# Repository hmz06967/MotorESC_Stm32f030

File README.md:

# MOTOR ESC CARD DESIGN FROM EAGLE CAD

Working please download and test 

#### video (https://www.youtube.com/watch?v=FIM-RrpVAwA)

firmware https://github.com/hmz06967/MotorEsc_Firmware

## Ekran Görüntüleri

#### Copyright (C) 2021 [OZK](https://hamzaozkan.com.tr)

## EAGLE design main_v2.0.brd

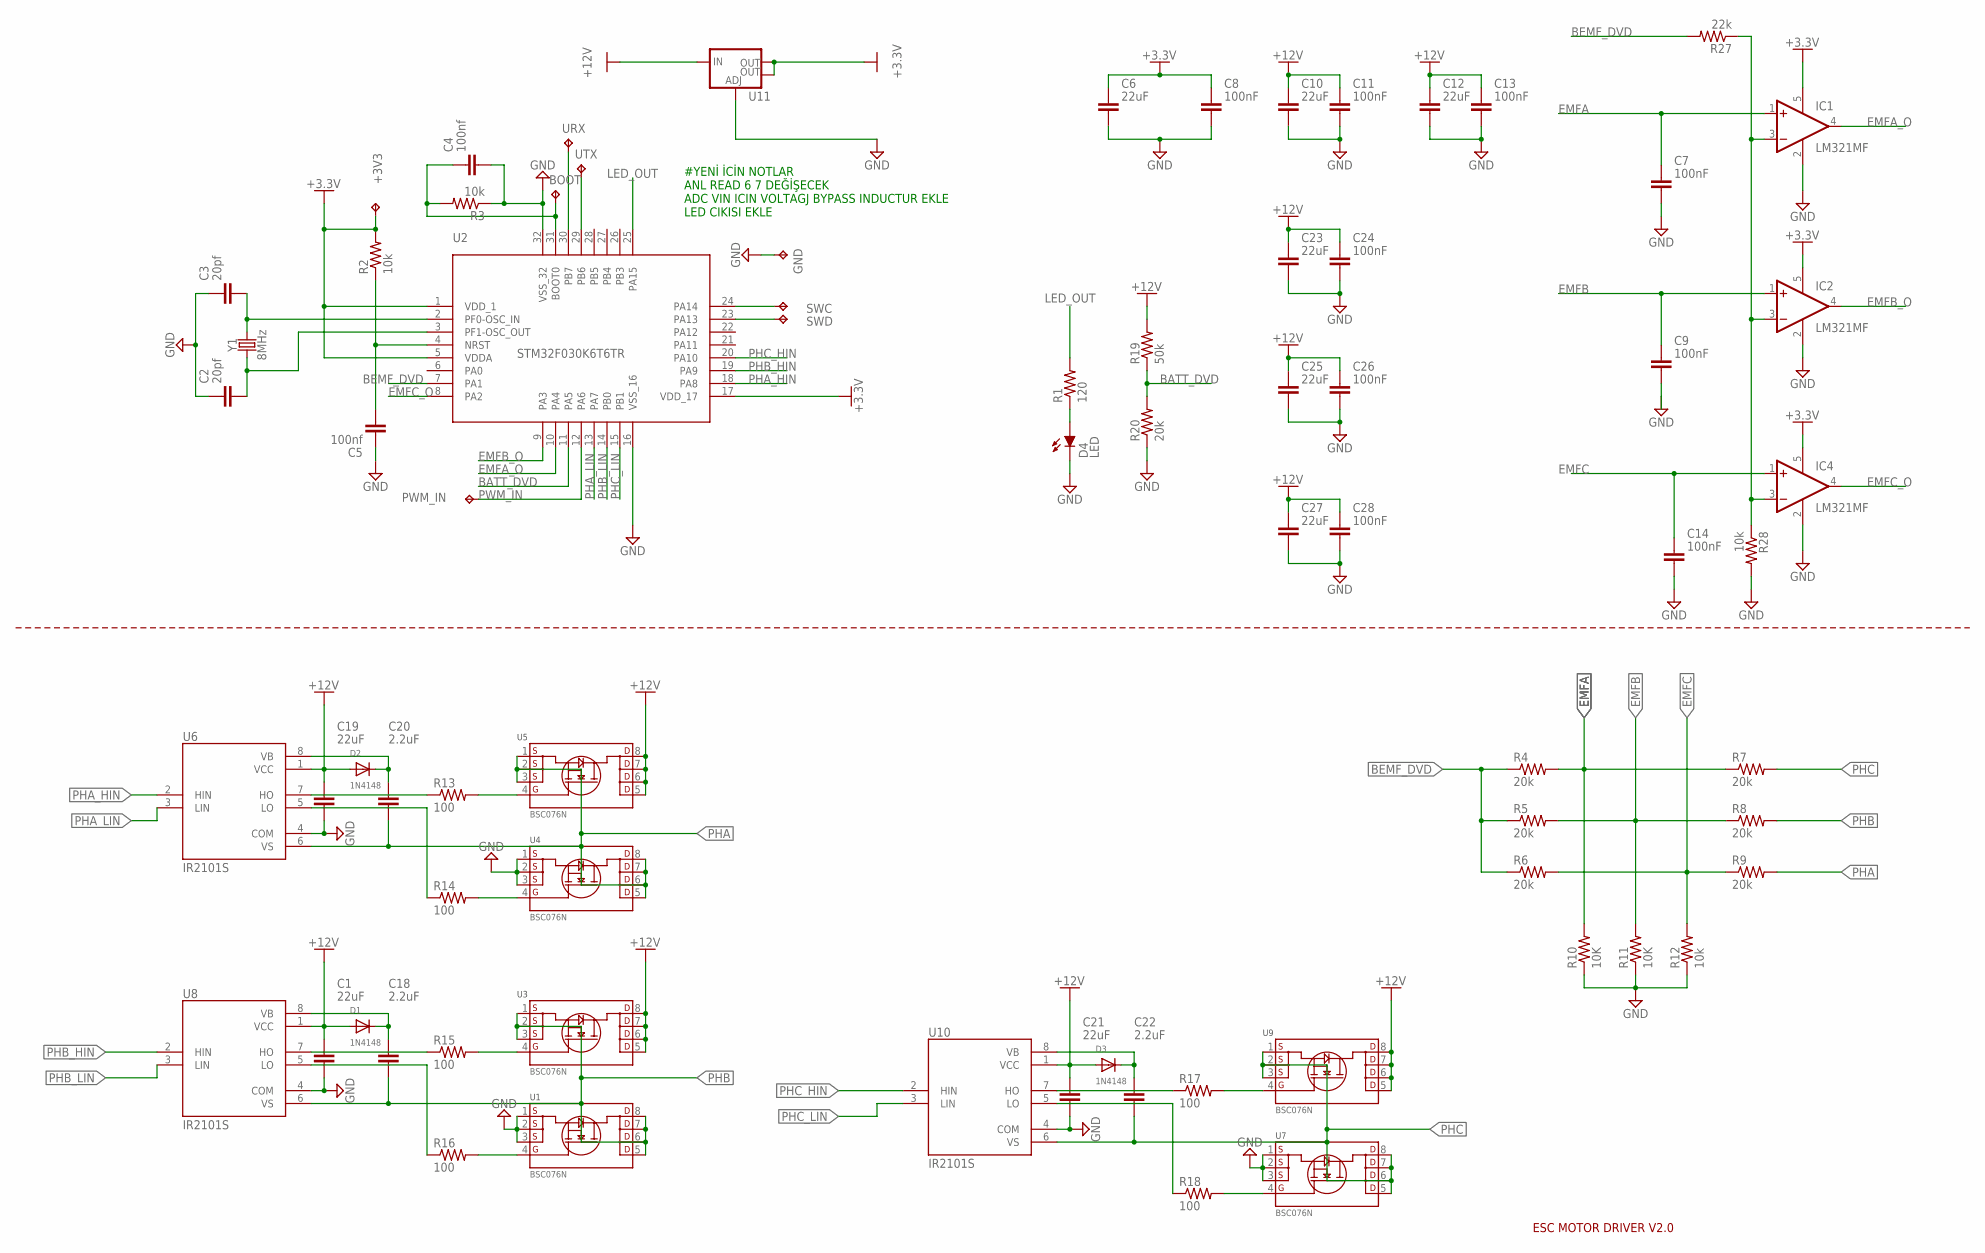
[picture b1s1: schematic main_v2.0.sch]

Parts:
+3V3: TPTP13R; TP13R
BOOT: TPTP13R; TP13R
C1, C6, C10, C12, C19, C21, C23, C25, C27: 22uF; CAPC3216X135
C2, C3: 20pf; CAPC1608X85
C4, C5: 100nf; CAPC2012X110
C7, C8, C9, C11, C13, C14, C24, C26, C28: 100nF; CAPC2012X110
C18, C20, C22: 2.2uF; CAPC3216X135
D1, D2, D3: 1N4148; SOD-323F
D4: LED; LED_CHIP-LED0603MP
GND: TPTP13R; TP13R
IC1, IC2, IC4: LM321MF; SOT23-5
PWM_IN: TPTP13R; TP13R
R1: 120; R0603
R2, R3, R12, R28: 10k; R0603
R4, R5, R6, R7, R8, R9, R20: 20k; R0603
R10, R11: 10K; R0603
R13, R14, R15, R16, R17, R18: 100; R0603
R19: 50k; R0603
R27: 22k; R0603
SWC: TPTP13R; TP13R
SWD: TPTP13R; TP13R
U1, U3, U4, U5, U7, U9: BSC076N; TRANS_BSC076N06NS3-G
U2: STM32F030K6T6TR; 32-LQFP
U6, U8, U10: IR2101S; SOIC127P600X175-8N
U11: V_REG_LM1117SOT223; SOT223
URX: TPTP13R; TP13R
UTX: TPTP13R; TP13R
Y1: 8MHz; CRYSTAL-SMD-5X3.2-4PAD

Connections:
+3.3V: +3V3.TP, C6.1, C8.1, IC1.5 (V+), IC2.5 (V+), IC4.5 (V+), R2.2, U2.1 (VDD_1), U2.5 (VDDA), U2.17 (VDD_17), U11.2 (OUT), U11.4 (OUT)
+12V: C1.1, C10.1, C11.1, C12.1, C13.1, C19.1, C21.1, C23.1, C24.1, C25.1, C26.1, C27.1, C28.1, D1.A, D2.A, D3.A, R19.2, U3.5 (D1), U3.6 (D2), U3.7 (D3), U3.8 (D4), U5.5 (D1), U5.6 (D2), U5.7 (D3), U5.8 (D4), U6.1 (VCC), U8.1 (VCC), U9.5 (D1), U9.6 (D2), U9.7 (D3), U9.8 (D4), U10.1 (VCC), U11.3 (IN)
BATT_DVD: R19.1, R20.2, U2.11 (PA5)
BEMF_DVD: R4.1, R5.1, R6.1, R27.2, U2.7 (PA1)
EMFA: C7.1, IC1.1 (+IN), R4.2, R7.1, R10.2
EMFA_O: IC1.4 (OUT), U2.10 (PA4)
EMFB: C9.1, IC2.1 (+IN), R5.2, R8.1, R11.2
EMFB_O: IC2.4 (OUT), U2.9 (PA3)
EMFC: C14.1, IC4.1 (+IN), R6.2, R9.1, R12.2
EMFC_O: IC4.4 (OUT), U2.8 (PA2)
GND: C1.2, C2.1, C3.1, C4.2, C5.1, C6.2, C7.2, C8.2, C9.2, C10.2, C11.2, C12.2, C13.2, C14.2, C19.2, C21.2, C23.2, C24.2, C25.2, C26.2, C27.2, C28.2, D4.C, GND.TP, IC1.2 (V-), IC2.2 (V-), IC4.2 (V-), R3.1, R10.1, R11.1, R12.1, R20.1, R28.2, U1.1 (S1), U1.2 (S2), U1.3 (S3), U2.16 (VSS_16), U2.32 (VSS_32), U4.1 (S1), U4.2 (S2), U4.3 (S3), U6.4 (COM), U7.1 (S1), U7.2 (S2), U7.3 (S3), U8.4 (COM), U10.4 (COM), U11.1 (ADJ)
LED_OUT: R1.2, U2.25 (PA15)
unnamed: C2.2, U2.3 (PF1-OSC_OUT), Y1.1
unnamed: C3.2, U2.2 (PF0-OSC_IN), Y1.3 (2)
unnamed: U2.30 (PB7), URX.TP
unnamed: C5.2, R2.1, U2.4 (NRST)
unnamed: BOOT.TP, C4.1, R3.2, U2.31 (BOOT0)
unnamed: U2.29 (PB6), UTX.TP
unnamed: IC1.3 (-IN), IC2.3 (-IN), IC4.3 (-IN), R27.1, R28.1
unnamed: SWC.TP, U2.24 (PA14)
unnamed: SWD.TP, U2.23 (PA13)
unnamed: D4.A, R1.1
unnamed: R15.1, U8.7 (HO)
unnamed: R16.1, U8.5 (LO)
unnamed: R15.2, U3.4 (G)
unnamed: C18.1, D1.C, U8.8 (VB)
unnamed: R16.2, U1.4 (G)
unnamed: R13.1, U6.7 (HO)
unnamed: R14.1, U6.5 (LO)
unnamed: C20.1, D2.C, U6.8 (VB)
unnamed: R14.2, U4.4 (G)
unnamed: R13.2, U5.4 (G)
unnamed: R17.1, U10.7 (HO)
unnamed: R18.1, U10.5 (LO)
unnamed: C22.1, D3.C, U10.8 (VB)
unnamed: R18.2, U7.4 (G)
unnamed: R17.2, U9.4 (G)
PHA: C20.2, R9.2, U4.5 (D1), U4.6 (D2), U4.7 (D3), U4.8 (D4), U5.1 (S1), U5.2 (S2), U5.3 (S3), U6.6 (VS)
PHA_HIN: U2.18 (PA8), U6.2 (HIN)
PHA_LIN: U2.13 (PA7), U6.3 (LIN)
PHB: C18.2, R8.2, U1.5 (D1), U1.6 (D2), U1.7 (D3), U1.8 (D4), U3.1 (S1), U3.2 (S2), U3.3 (S3), U8.6 (VS)
PHB_HIN: U2.19 (PA9), U8.2 (HIN)
PHB_LIN: U2.14 (PB0), U8.3 (LIN)
PHC: C22.2, R7.2, U7.5 (D1), U7.6 (D2), U7.7 (D3), U7.8 (D4), U9.1 (S1), U9.2 (S2), U9.3 (S3), U10.6 (VS)
PHC_HIN: U2.20 (PA10), U10.2 (HIN)
PHC_LIN: U2.15 (PB1), U10.3 (LIN)
PWM_IN: PWM_IN.TP, U2.12 (PA6)

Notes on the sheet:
ESC MOTOR DRIVER V2.0
#YENİ İCİN NOTLAR ANL READ 6 7 DEĞİŞECEK ADC VIN ICIN VOLTAGJ BYPASS INDUCTUR EKLE LED CIKISI EKLE

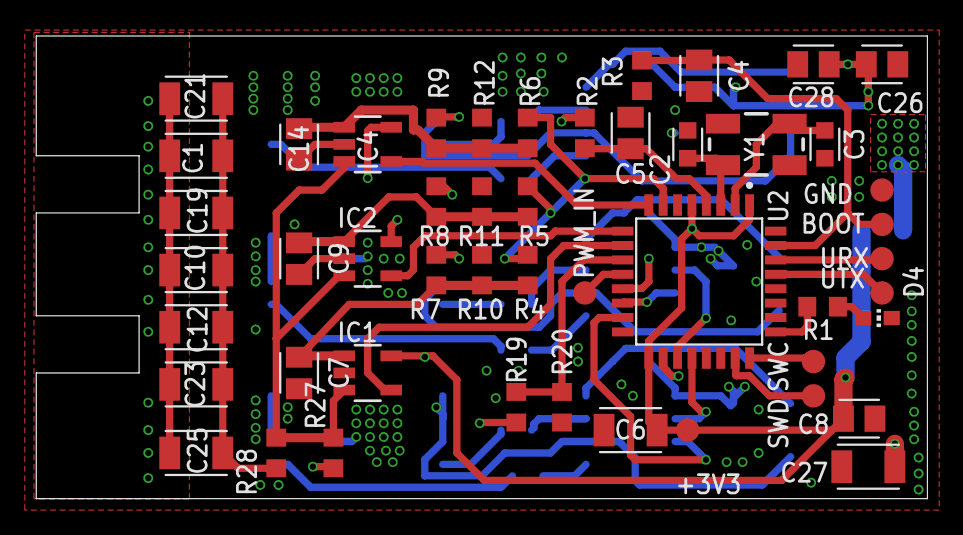
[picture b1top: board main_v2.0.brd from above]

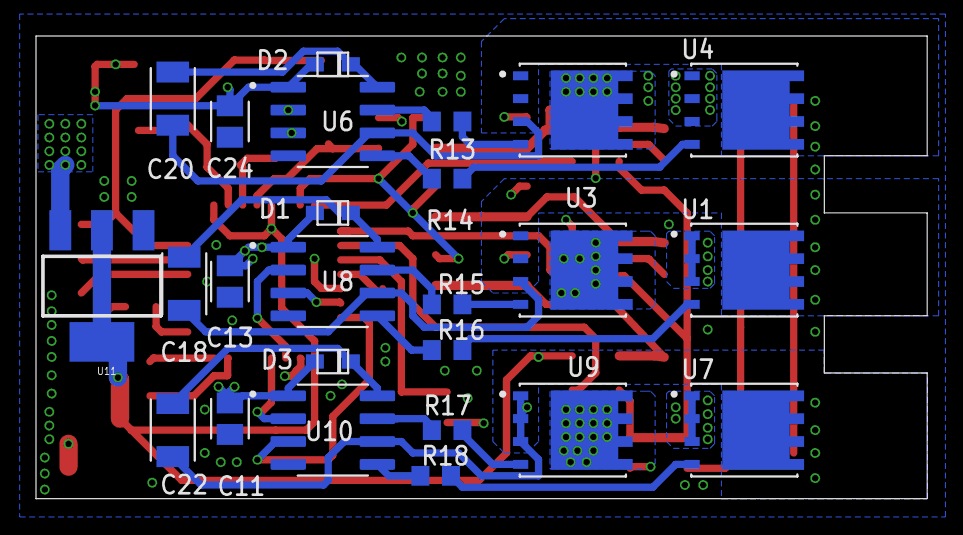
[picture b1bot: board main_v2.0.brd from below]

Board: 4 copper layers, 49.5 x 25.7 mm, 74 parts (25 on the bottom side), 47 nets.

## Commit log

2022-12-29 add files
2023-01-15 updated ldo regulator
    we are tested working project
2023-01-15 updated image

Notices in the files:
parts and their libraries:
SparkFun-Clocks: Licensing: Creative Commons ShareAlike 4.0 International - https://creativecommons.org/licenses/by-sa/4.0
